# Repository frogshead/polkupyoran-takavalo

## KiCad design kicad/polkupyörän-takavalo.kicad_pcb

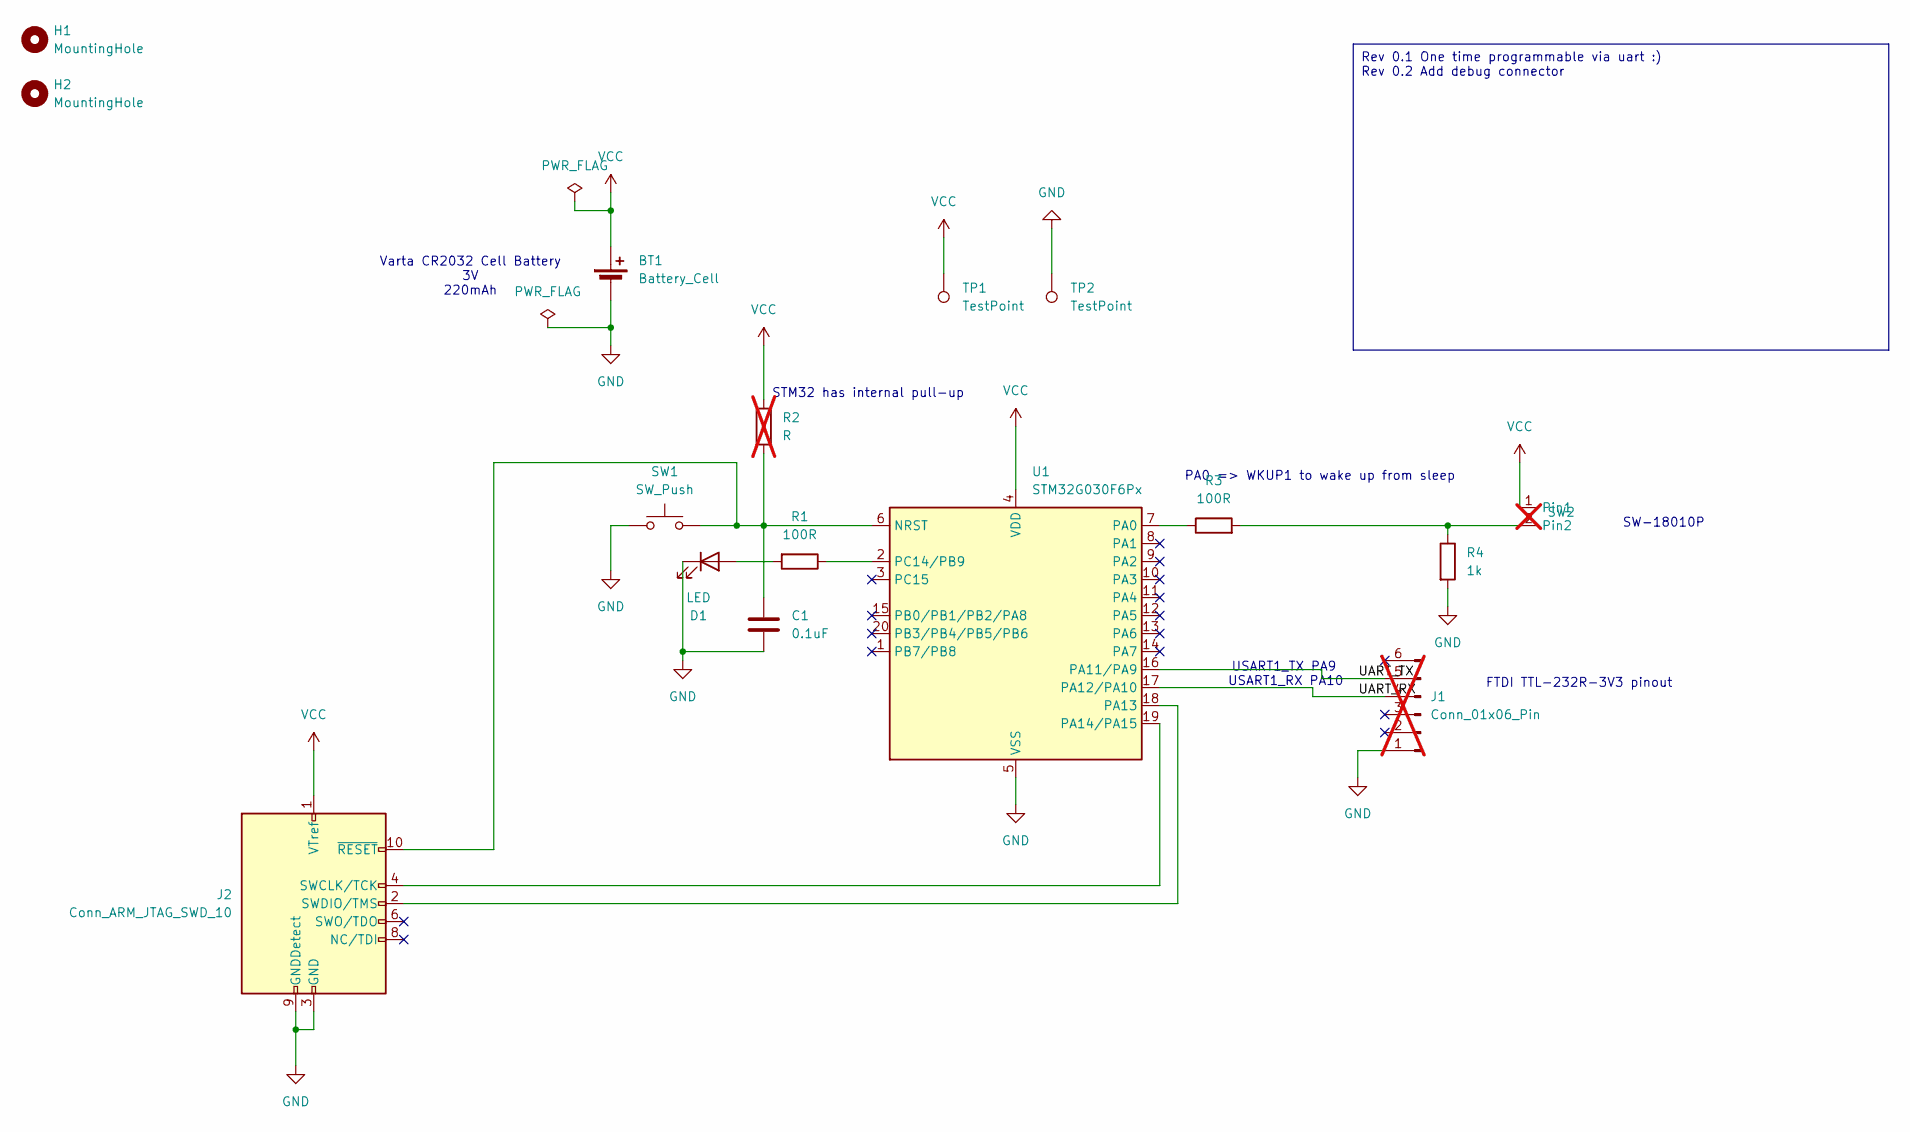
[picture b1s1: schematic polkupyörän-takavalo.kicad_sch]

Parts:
BT1: Battery_Cell; BatteryHolder_Multicomp_BC-2001_1x2032; LCSC C964824
C1: 0.1uF; C_0603_1608Metric_Pad1.08x0.95mm_HandSolder; LCSC C14663
D1: LED; LED_0603_1608Metric; LCSC C2286
H1, H2: MountingHole; MountingHole_3.2mm_M3
J1: Conn_01x06_Pin; PinSocket_1x06_P2.54mm_Horizontal; not fitted
J2: Conn_ARM_JTAG_SWD_10; PinHeader_2x05_P1.27mm_Vertical_SMD; LCSC C42372555
R1, R3: 100R; R_0603_1608Metric_Pad0.98x0.95mm_HandSolder; LCSC C105588
R2: R; R_0603_1608Metric_Pad0.98x0.95mm_HandSolder; not fitted
R4: 1k; R_0603_1608Metric_Pad0.98x0.95mm_HandSolder; LCSC C14676
SW1: SW_Push; SW_Push_1P1T_NO_6x6mm_H9.5mm; LCSC C111373
SW2: LED_D3.0mm; LCSC C2681585; not fitted
TP1, TP2: TestPoint; TestPoint_Pad_2.0x2.0mm
U1: STM32G030F6Px; TSSOP-20_4.4x6.5mm_P0.65mm; LCSC C529330

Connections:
/UART_RX: J1.4, U1.17 (PA12/PA10)
/UART_TX: J1.5, U1.16 (PA11/PA9)
GND: BT1.2 (-), C1.2, D1.1 (K), J1.1, J2.3 (GND), J2.5 (GND), J2.9 (GNDDetect), R4.2, SW1.1, TP2.1, U1.5 (VSS)
unnamed: D1.2 (A), R1.2
unnamed: J2.4 (SWCLK/TCK), U1.19 (PA14/PA15)
unnamed: J2.2 (SWDIO/TMS), U1.18 (PA13)
unnamed: C1.1, J2.10 (~RESET), R2.2, SW1.2, U1.6 (NRST)
unnamed: R3.2, R4.1, SW2.2 (Pin2)
unnamed: R3.1, U1.7 (PA0)
unnamed: R1.1, U1.2 (PC14/PB9)
VCC: BT1.1 (+), J2.1 (VTref), R2.1, SW2.1 (Pin1), TP1.1, U1.4 (VDD)

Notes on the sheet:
Rev 0.1 One time programmable via uart :) Rev 0.2 Add debug connector
SW-18010P
USART1_TX PA9
USART1_RX PA10
PA0 => WKUP1 to wake up from sleep
FTDI TTL-232R-3V3 pinout
Varta CR2032 Cell Battery 3V 220mAh
STM32 has internal pull-up

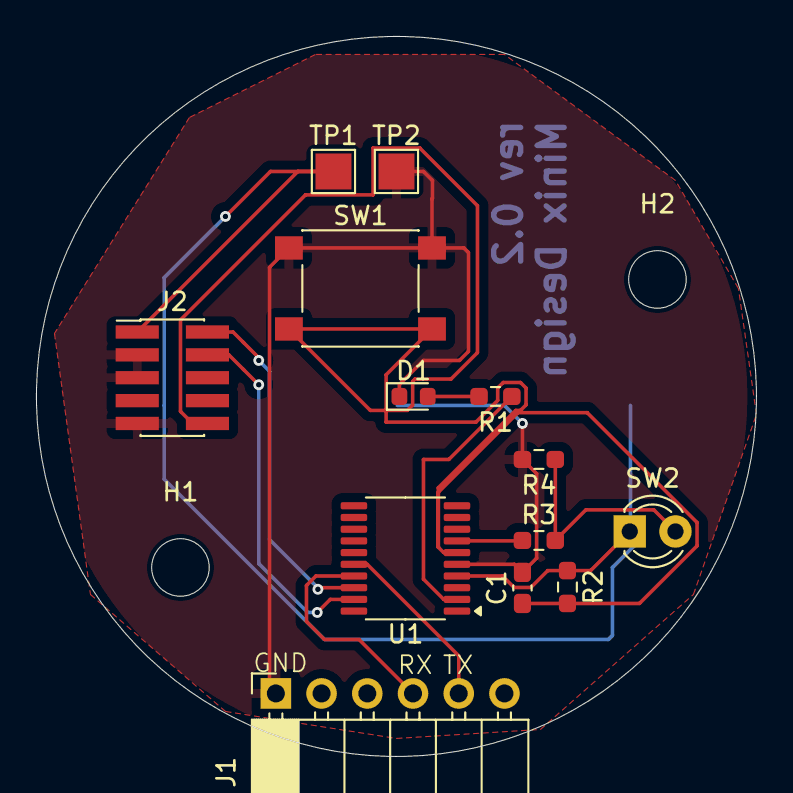
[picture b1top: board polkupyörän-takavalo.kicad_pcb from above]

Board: 2 copper layers, 40.0 x 40.0 mm, 16 parts (1 on the bottom side), 11 nets.

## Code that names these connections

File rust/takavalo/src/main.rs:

#![no_std]
#![no_main]

// use cortex_m::{asm::delay, delay::{self, Delay}, prelude::_embedded_hal_blocking_delay_DelayUs};
use embassy_executor::Spawner;
use {defmt_rtt as _, panic_probe as _};
use embassy_time::Timer;
use embassy_stm32::gpio::{Input, Level, Output, Pull, Speed};
use embassy_stm32::usart::{Config, Uart};
use embassy_stm32::{bind_interrupts, peripherals, usart};
use embassy_stm32::exti::ExtiInput;
use embassy_stm32::rtc::{DateTime, DayOfWeek, Rtc, RtcConfig};
// use embassy_stm32::adc::Adc;
// use embassy_stm32::rcc::Config as ClockConfig;
use defmt::info;
use core::str::FromStr;
use chrono::{DateTime as chronoDateTime, Datelike, Timelike};

const BUILD_TIMESTAMP: &str = env!("BUILD_TIMESTAMP");



bind_interrupts!(struct Irqs {
    USART1 => usart::InterruptHandler<peripherals::USART1>;
});

#[embassy_executor::main]
async fn main(_spawner: Spawner) {
    let p = embassy_stm32::init(Default::default());
    let mut config = Config::default();
    config.baudrate = 115200;
    let mut usart = Uart::new(p.USART1, p.PA10, p.PA9, Irqs,p.DMA1_CH2, p.DMA1_CH3, config).unwrap();
    usart.write(b"Hello Embassy World!\r\n").await.unwrap();
    info!("wrote Hello, starting echo");

    // Configure PA0 as input with pull-down
    let button = Input::new(p.PA0, Pull::Down);
    // Configure EXTI (External Interrupt) on PA0
    let mut exti = ExtiInput::new(button,p.EXTI0);
    let mut led = Output::new(p.PB9, Level::High, Speed::Low);
    let timestamp = i64::from_str(BUILD_TIMESTAMP).expect("Invalid timestamp");

    // Parse the timestamp into a `NaiveDateTime`
    let datetime = chronoDateTime::from_timestamp(timestamp, 0)
       .expect("Failed to parse timestamp");
    // info!("Datetime from build: {:?}", datetime.to_string());

    let now = DateTime::from(datetime.year().try_into().unwrap(),
    datetime.month().try_into().unwrap(),
    datetime.day().try_into().unwrap(),
    match datetime.weekday() {
        chrono::Weekday::Mon => DayOfWeek::Monday,
        chrono::Weekday::Tue => DayOfWeek::Tuesday,
        chrono::Weekday::Wed => DayOfWeek::Wednesday,
        chrono::Weekday::Thu => DayOfWeek::Thursday,
        chrono::Weekday::Fri => DayOfWeek::Friday,
        chrono::Weekday::Sat => DayOfWeek::Saturday,
        chrono::Weekday::Sun => DayOfWeek::Sunday,
    },
    datetime.hour().try_into().unwrap(),
    datetime.minute().try_into().unwrap(),
    datetime.second().try_into().unwrap());

    let mut rtc = Rtc::new(p.RTC, RtcConfig::default());
    

    rtc.set_datetime(now.unwrap()).expect("datetime not set");
    let now: DateTime = rtc.now().unwrap().into();

    info!("{}:{}:{}", now.hour(), now.minute(), now.second());
    
    //let mut clk_config = ClockConfig::default();
    
    // let delay = Delay::new(p.SYSCFG., ahb_frequency).delay_us(200);
    
    // let mut adc = Adc::new(p.ADC1, delay);
    // // Blinking 30s and then try to sleep and waiting for interrupt
    loop {
        info!("Toggling LED");
        for _ in 0..100{
            Timer::after_millis(300).await;
            led.toggle();
        }
        led.set_low();
        exti.wait_for_rising_edge().await;
    }
}

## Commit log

2024-05-19 Add gitignore
2024-05-19 order created to jlcpcb
2024-05-19 reorganize
2024-05-19 own folders for kicad and rust
2024-05-19 compiles
2024-05-19 rust workflow with working dir
2024-05-19 test
2024-05-19 poors man version of the cycling light
2024-06-01 Add pdf version of the schematics
2024-06-01 turn off the led before sleep
2024-06-04 Light off the led before going to sleep
2024-06-09 try to set boot options so that we are able to boot after the first programming
2025-02-09 Prepare to v2, update readme, add usart and RTC from examples
2025-02-11 version 2
2025-02-12 remove old pdf schematic
2025-03-07 use timestamp from build to set rtc time
2025-03-07 fix target architecture on runner configuration
